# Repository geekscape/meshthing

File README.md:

meshthing
=========

MeshThing module: Hardware and software repository

Current version is v1.2.

Contents:
----------
-Hardware - Source files for PCB production.

-Software - Source files for testing and use.

-Resources - Additional utilities and documentation.

-Reference - Mostly datasheets.

Pinout:

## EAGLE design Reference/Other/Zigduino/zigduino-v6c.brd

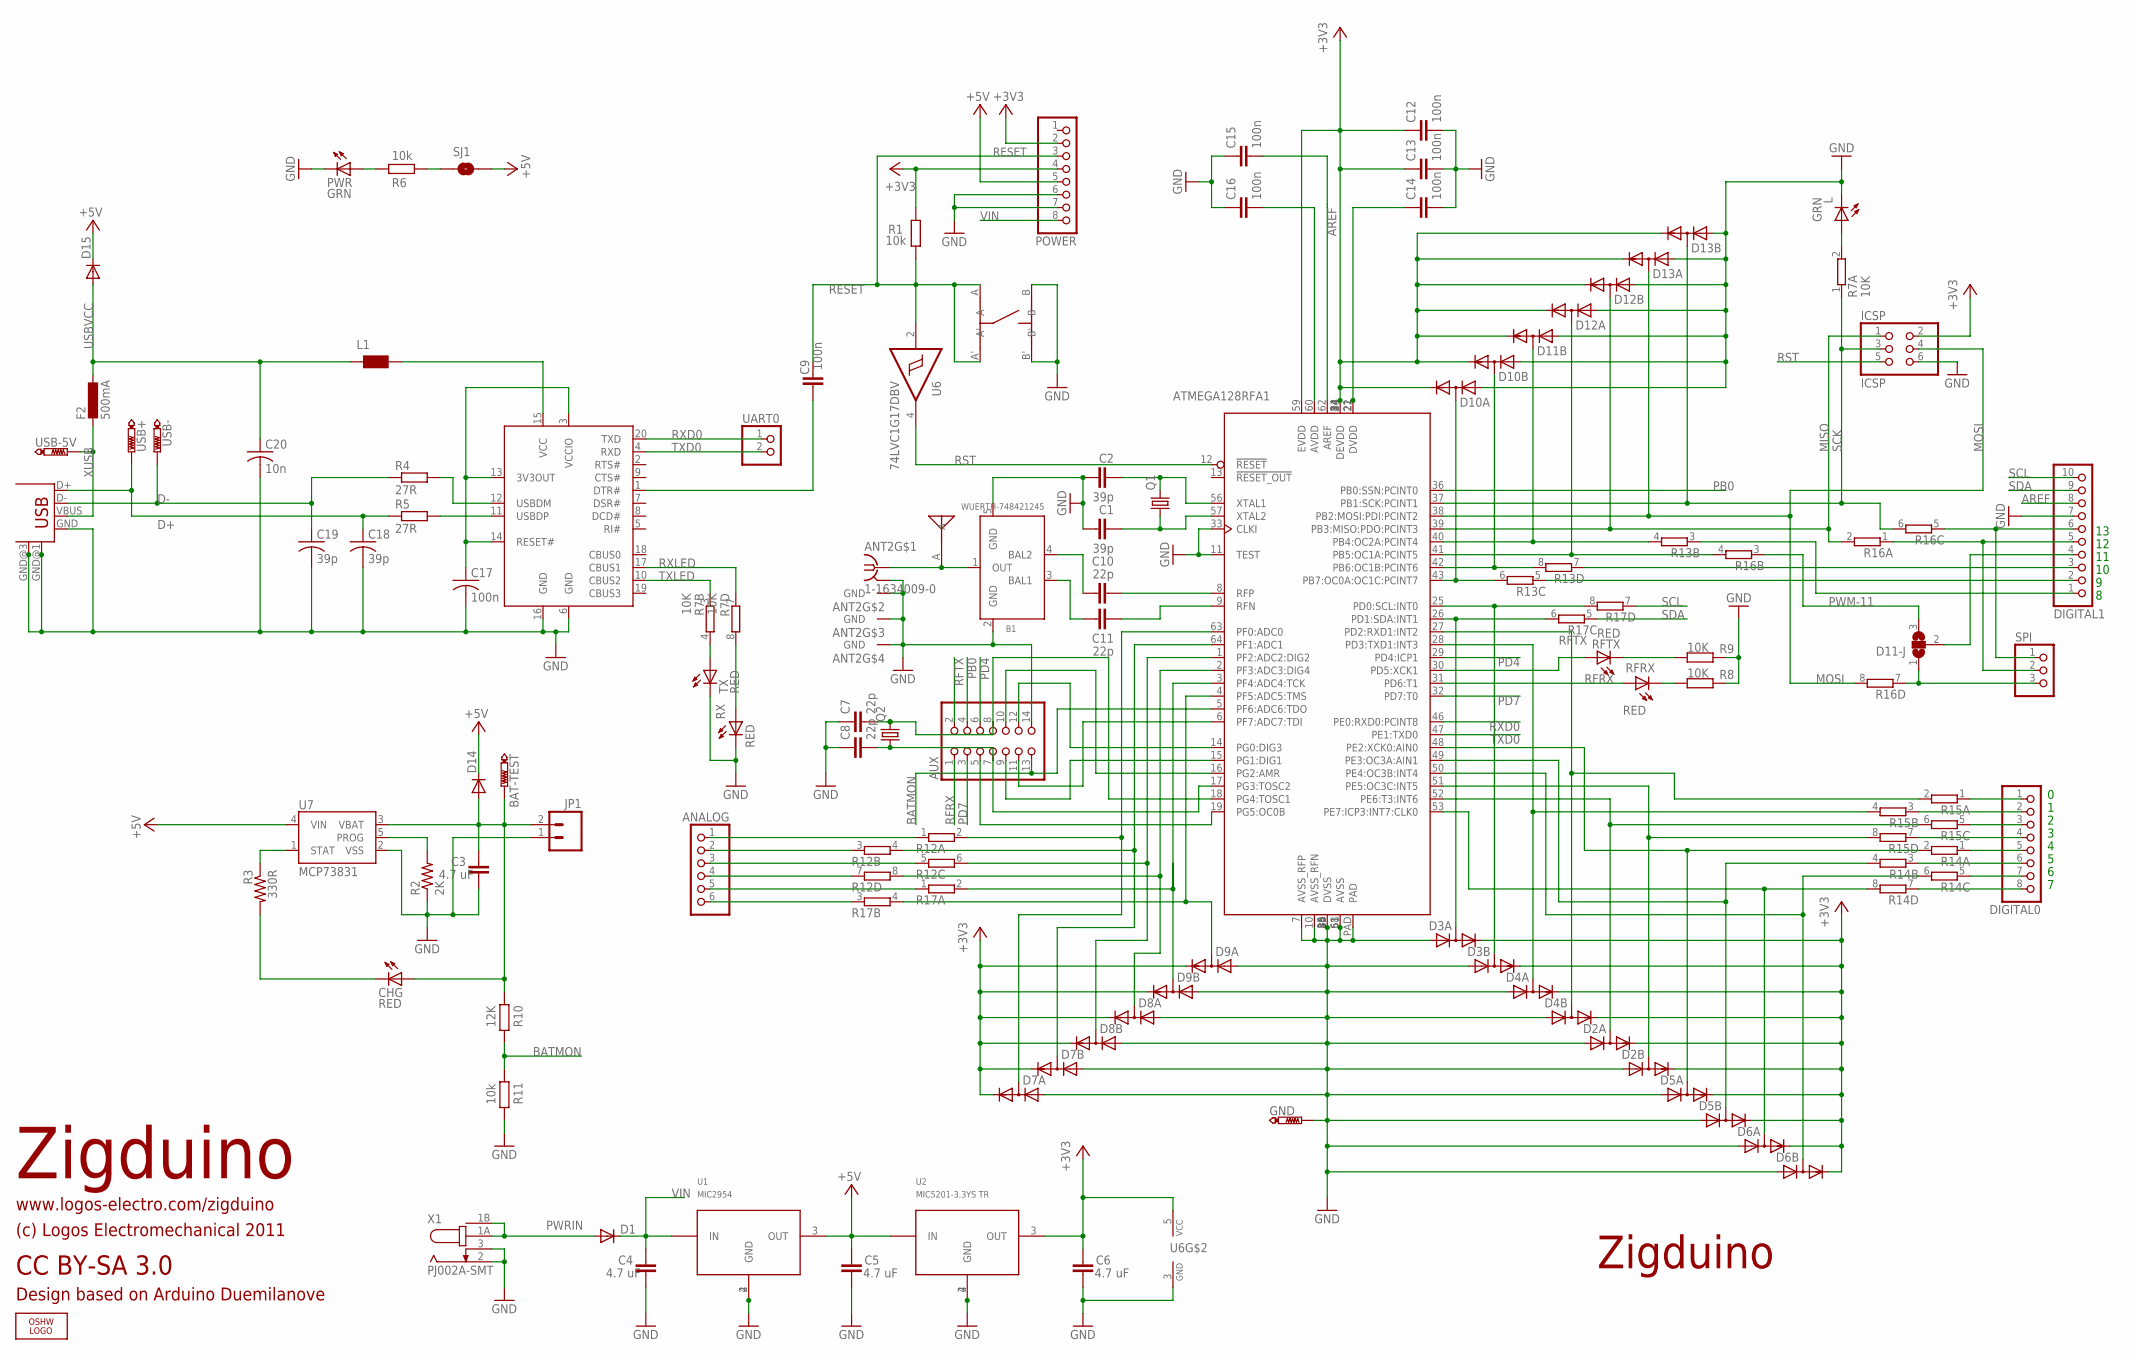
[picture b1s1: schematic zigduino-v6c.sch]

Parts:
ANALOG: PINHD-1X6; 1X06; PARTNO 19742
ANT1: MOLEX-ANT; PARTNO 0479480001
ANT2: 1-1634009-0; MMCX-THRU
AUX: PINHD-2X7_2.00; 2X07M; PARTNO 00217
B1: WUERTH-748421245; WURTH-BALUN; PARTNO 748421245
BAT-TEST: PTR1TP13SQ; TP13SQ; PARTNO TP13
C1, C2, C18, C19: 39p; C0603; PARTNO C1608C0G1H390J
C3, C4, C5, C6: 4.7 uF; C1206; PARTNO C3216Y5V1H475Z
C7, C8, C10, C11: 22p; C0603; PARTNO GQM1885C1H220JB01D
C9, C12, C13, C14, C15, C16, C17: 100n; C0603; PARTNO CC0603MRY5V9BB104
C20: 10n; C0603; PARTNO GRM188R71H103KA01D
CHG: RED; CHIP-LED0603; PARTNO LTST-C193KRKT-5A
D1, D14, D15: DIODE-SMB; SMB; PARTNO B150B-13-F
D2, D3, D4, D5, D6, D7, D8, D9, D10, D11, D12, D13: SD103ASDM; SOT26; PARTNO SD103ASDM-7
D11-J: SJ2W; SJ_2; PARTNO SJ3
DIGITAL0: PINHD-1X8; 1X08; PARTNO 19743
DIGITAL1: PINHD-1X10; 1X10; PARTNO 20083
F2: 500mA; L1812; PARTNO MF-MSMF050-2
GND: PTR1TP13SQ; TP13SQ; PARTNO TP13
ICSP: ICSP; 2X03; PARTNO 961206-6404-AR
JP1: M02-JST-2MM-SMT; S2B-PH; PARTNO S2B-PH-SM4-TB(LF)(SN)
L: GRN; CHIP-LED0603; PARTNO LTST-C193KGKT-5A
L1: WE-CBF_0805; 0805; PARTNO MI0805K400R-10
LOGO1: OSHW_LOGO_FILLX0200-NT; OSHW_FILLX200_NOTEXT
POWER: PINHD-1X8; 1X08; PARTNO 19743
PWR: GRN; CHIP-LED0603; PARTNO LTST-C193KGKT-5A
Q1: CRYSTALCSM-3X; CSM-3X; PARTNO ECS-160-20-3X-TR
Q2: CRYSTALTC26H; TC26H
R1, R6, R11: 10k; R0603; PARTNO RMCF0603FT10K0
R2: 2K; R0603; PARTNO RC0603FR-072KL
R3: 330R; R0603; PARTNO RC0603FR-07330RL
R4, R5: 27R; R0603; PARTNO RC0603JR-0727RL
R7: 10K; CTS742C083-RES; PARTNO 742C083103JPTR
R8, R9: 10K; R0603; PARTNO RMCF0603FT10K0
R10: 12K; R0603; PARTNO RMCF0603FT12K0
R12, R13, R14, R15, R16, R17: 4R-NCTS742C083; CTS742C083-RES; PARTNO 742C083101JPTR
RFRX: RED; CHIP-LED0603; PARTNO LTST-C193KRKT-5A
RFTX: RED; CHIP-LED0603; PARTNO LTST-C193KRKT-5A
RX: RED; CHIP-LED0603; PARTNO LTST-C193KRKT-5A
SJ1: SOLDERJUMPERTRACE; SJ_2S-TRACE
SPI: PINHD-1X3; 1X03; PARTNO 20152
SW1: EVQ-PSD02K; EVQPSD02K; PARTNO EVQ-PSD02K
TX: RED; CHIP-LED0603; PARTNO LTST-C193KRKT-5A
U1: MIC2954; SOT223; PARTNO MIC2954-03WS-TR
U2: MIC5201-3.3YS TR; SOT223; PARTNO MIC5201-3.3YS TR
U3: ATMEGA128RFA1; QFN64; PARTNO ATMEGA128RFA1-ZUR
U4: FT231XS-R; SSOP20; PARTNO FT231XS-R
U6: 74LVC1G17DBV; SOT23-5; PARTNO SN74LVC1G17DBVR
U7: MCP73831; SOT23-5; PARTNO MCP73831T-2ACI/OT
UART0: PINHD-1X2; 1X02; PARTNO 00522
USB: USB-MB-S; PARTNO 20236
USB+: PTR1TP13SQ; TP13SQ; PARTNO TP13
USB-, USB-5V: PTR1TP13SQ; TP13SQ; PARTNO TP13
X1: PJ002A-SMT; PARTNO PJ-002AH-SMT

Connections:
+3V3: C6.1, C12.1, C13.1, D2.2 (C), D2.5 (C), D3.2 (C), D3.5 (C), D4.2 (C), D4.5 (C), D5.2 (C), D5.5 (C), D6.2 (C), D6.5 (C), D7.2 (C), D7.5 (C), D8.2 (C), D8.5 (C), D9.2 (C), D9.5 (C), D10.2 (C), D10.5 (C), D11.5 (C), D12.2 (C), D12.5 (C), D13.2 (C), D13.5 (C), ICSP.2, POWER.2, POWER.4, R1.2, U2.3 (OUT), U3.23 (DEVDD), U3.34 (DEVDD), U3.44 (DEVDD), U3.54 (DEVDD), U3.59 (EVDD), U6.5 (VCC)
+5V: C5.1, D14.C, D15.C, POWER.5, SJ1.2, U1.3 (OUT), U2.1 (IN), U7.4 (VIN)
AREF: C15.2, DIGITAL1.8, U3.62 (AREF)
BATMON: AUX.13, R10.2, R11.1, U3.5 (PF6:ADC6:TDO)
D+: C18.1, R5.1, USB.D+, USB+.TP
D-: C19.1, R4.1, USB.D-, USB-.TP
DTR: C9.1, U4.1 (DTR#)
GND: ANT2.G@0 (GND), ANT2.G@1 (GND), ANT2.G@2 (GND), ANT2.G@3 (GND), AUX.14, B1.2 (GND), B1.5 (GND), C1.1, C2.1, C3.2, C4.2, C5.2, C6.2, C7.1, C8.1, C12.2, C13.2, C14.2, C15.1, C16.1, C17.2, C18.2, C19.2, C20.2, D2.3 (A), D2.6 (A), D3.3 (A), D3.6 (A), D4.3 (A), D4.6 (A), D5.3 (A), D5.6 (A), D6.3 (A), D6.6 (A), D7.3 (A), D7.6 (A), D8.3 (A), D8.6 (A), D9.3 (A), D9.6 (A), D10.3 (A), D10.6 (A), D11.6 (A), D12.3 (A), D12.6 (A), D13.3 (A), D13.6 (A), DIGITAL1.7, GND.TP, ICSP.6, JP1.1, L.C, POWER.6, POWER.7, PWR.C, R2.1, R8.1, R9.1, R11.2, RX.C, SW1.B, SW1.B', TX.C, U1.2 (GND), U1.4 (GND), U2.2 (GND), U2.4 (GND), U3.7 (AVSS_RFP), U3.10 (AVSS_RFN), U3.11 (TEST), U3.20 (DVSS), U3.24 (DVSS), U3.33 (CLKI), U3.35 (DVSS), U3.45 (DVSS), U3.55 (DVSS), U3.58 (AVSS), U3.61 (AVSS), U3.PAD, U4.6 (GND), U4.16 (GND), U6.3 (GND), U7.2 (VSS), USB.GND, USB.GND@1 (GND), USB.GND@3 (GND), X1.2, X1.3
MISO: D12.1 (AC), ICSP.1, R16.2, U3.39 (PB3:MISO:PDO:PCINT3)
MOSI: D13.4 (AC), ICSP.4, R16.8 (2), U3.38 (PB2:MOSI:PDI:PCINT2)
MOSI-PIN: D11-J.1, R16.7 (1), SPI.3
unnamed: R9.2, RFTX.C
unnamed: L.A, R7.2
unnamed: PWR.A, R6.2
unnamed: B1.4 (BAL2), C10.1
unnamed: DIGITAL0.3, R15.5 (1)
unnamed: C1.2, Q1.1, U3.57 (XTAL2)
unnamed: C2.2, Q1.2, U3.56 (XTAL1)
unnamed: R6.1, SJ1.1
unnamed: B1.3 (BAL1), C11.1
unnamed: DIGITAL1.5, R16.1, SPI.2
unnamed: DIGITAL0.5, R14.1
unnamed: DIGITAL0.7, R14.5 (1)
unnamed: DIGITAL0.6, R14.3 (1)
unnamed: DIGITAL0.4, R15.7 (1)
unnamed: DIGITAL0.8, R14.7 (1)
unnamed: D3.1 (AC), R17.8 (2), U3.25 (PD0:SCL:INT0)
unnamed: D3.4 (AC), R17.6 (2), U3.26 (PD1:SDA:INT1)
unnamed: ANT1.A, ANT2.C (1), B1.1 (OUT)
unnamed: D12.4 (AC), R16.4 (2), U3.41 (PB5:OC1A:PCINT5)
unnamed: R8.2, RFRX.C
unnamed: D2.4 (AC), R15.6 (2), U3.52 (PE6:T3:INT6)
unnamed: D2.1 (AC), R15.8 (2), U3.51 (PE5:OC3C:INT5)
unnamed: C10.2, U3.8 (RFP)
unnamed: C11.2, U3.9 (RFN)
unnamed: DIGITAL1.6, R16.5 (1), SPI.1
unnamed: R2.2, U7.5 (PROG)
unnamed: R3.1, U7.1 (STAT)
unnamed: CHG.C, R3.2
unnamed: C17.1, U4.3 (VCCIO), U4.13 (3V3OUT), U4.14 (RESET#)
unnamed: R7.4 (2), TX.A
unnamed: R7.8 (2), RX.A
unnamed: D11.1 (AC), R13.4 (2), U3.40 (PB4:OC2A:PCINT4)
unnamed: R4.2, U4.12 (USBDM)
unnamed: R5.2, U4.11 (USBDP)
unnamed: L1.2, U4.15 (VCC)
unnamed: D10.1 (AC), R13.8 (2), U3.42 (PB6:OC1B:PCINT6)
unnamed: D10.4 (AC), R13.6 (2), U3.43 (PB7:OC0A:OC1C:PCINT7)
unnamed: D5.4 (AC), R14.2, U3.48 (PE2:XCK0:AIN0)
unnamed: D6.1 (AC), R14.6 (2), U3.50 (PE4:OC3B:INT4)
unnamed: D5.1 (AC), R14.4 (2), U3.49 (PE3:OC3A:AIN1)
unnamed: D6.4 (AC), R14.8 (2), U3.53 (PE7:ICP3:INT7:CLK0)
unnamed: ANALOG.5, R17.1
unnamed: ANALOG.6, R17.3 (1)
unnamed: AUX.11, U3.6 (PF7:ADC7:TDI)
unnamed: D7.4 (AC), R12.2, U3.63 (PF0:ADC0)
unnamed: D7.1 (AC), R12.4 (2), U3.64 (PF1:ADC1)
unnamed: D8.1 (AC), R12.6 (2), U3.1 (PF2:ADC2:DIG2)
unnamed: D8.4 (AC), R12.8 (2), U3.2 (PF3:ADC3:DIG4)
unnamed: D9.1 (AC), R17.2, U3.3 (PF4:ADC4:TCK)
unnamed: D9.4 (AC), R17.4 (2), U3.4 (PF5:ADC5:TMS)
unnamed: ANALOG.1, R12.1
unnamed: ANALOG.2, R12.3 (1)
unnamed: ANALOG.3, R12.5 (1)
unnamed: ANALOG.4, R12.7 (1)
unnamed: DIGITAL1.1, R13.3 (1)
unnamed: D11-J.2, DIGITAL1.4
unnamed: AUX.12, U3.14 (PG0:DIG3)
unnamed: C14.1, U3.21 (DVDD), U3.22 (DVDD)
unnamed: C16.2, U3.60 (AVDD)
unnamed: DIGITAL1.2, R13.5 (1)
unnamed: DIGITAL0.1, R15.1
unnamed: DIGITAL0.2, R15.3 (1)
unnamed: AUX.9, U3.15 (PG1:DIG1)
unnamed: AUX.5, U3.19 (PG5:OC0B)
unnamed: AUX.8, C7.2, Q2.2, U3.18 (PG4:TOSC1)
unnamed: AUX.7, C8.2, Q2.1, U3.17 (PG3:TOSC2)
unnamed: AUX.10, U3.16 (PG2:AMR)
PB0: AUX.4, U3.36 (PB0:SSN:PCINT0)
PD4: AUX.6, U3.29 (PD4:ICP1)
PD7: AUX.3, U3.32 (PD7:T0)
PWM-10: DIGITAL1.3, R13.7 (1)
PWM-11: D11-J.3, R16.3 (1)
PWRIN: D1.A, X1.1A, X1.1B
RESET: C9.2, POWER.3, R1.1, SW1.A, SW1.A', U6.2 (I)
RFRX: AUX.1, RFRX.A, U3.31 (PD6:T1)
RFTX: AUX.2, RFTX.A, U3.30 (PD5:XCK1)
RST: ICSP.5, U3.12 (!RESET!), U6.4 (O)
RXD0: U3.46 (PE0:RXD0:PCINT8), U4.20 (TXD), UART0.1
RXD1: D4.1 (AC), R15.2, U3.27 (PD2:RXD1:INT2)
RXLED: R7.7 (1), U4.17 (CBUS1)
SCK: D13.1 (AC), ICSP.3, R7.1, R16.6 (2), U3.37 (PB1:SCK:PCINT1)
SCL: DIGITAL1.10, R17.7 (1)
SDA: DIGITAL1.9, R17.5 (1)
TXD0: U3.47 (PE1:TXD0), U4.4 (RXD), UART0.2
TXD1: D4.4 (AC), R15.4 (2), U3.28 (PD3:TXD1:INT3)
TXLED: R7.3 (1), U4.10 (CBUS2)
USBVCC: C20.1, D15.A, F2.1, L1.1
VBAT: BAT-TEST.TP, C3.1, CHG.A, D14.A, JP1.2, R10.1, U7.3 (VBAT)
VIN: C4.1, D1.C, POWER.8, U1.1 (IN)
XUSB: F2.2, USB.VBUS, USB-5V.TP

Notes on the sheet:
Zigduino
CC BY-SA 3.0
(c) Logos Electromechanical 2011
www.logos-electro.com/zigduino
ATMEGA128RFA1
Design based on Arduino Duemilanove

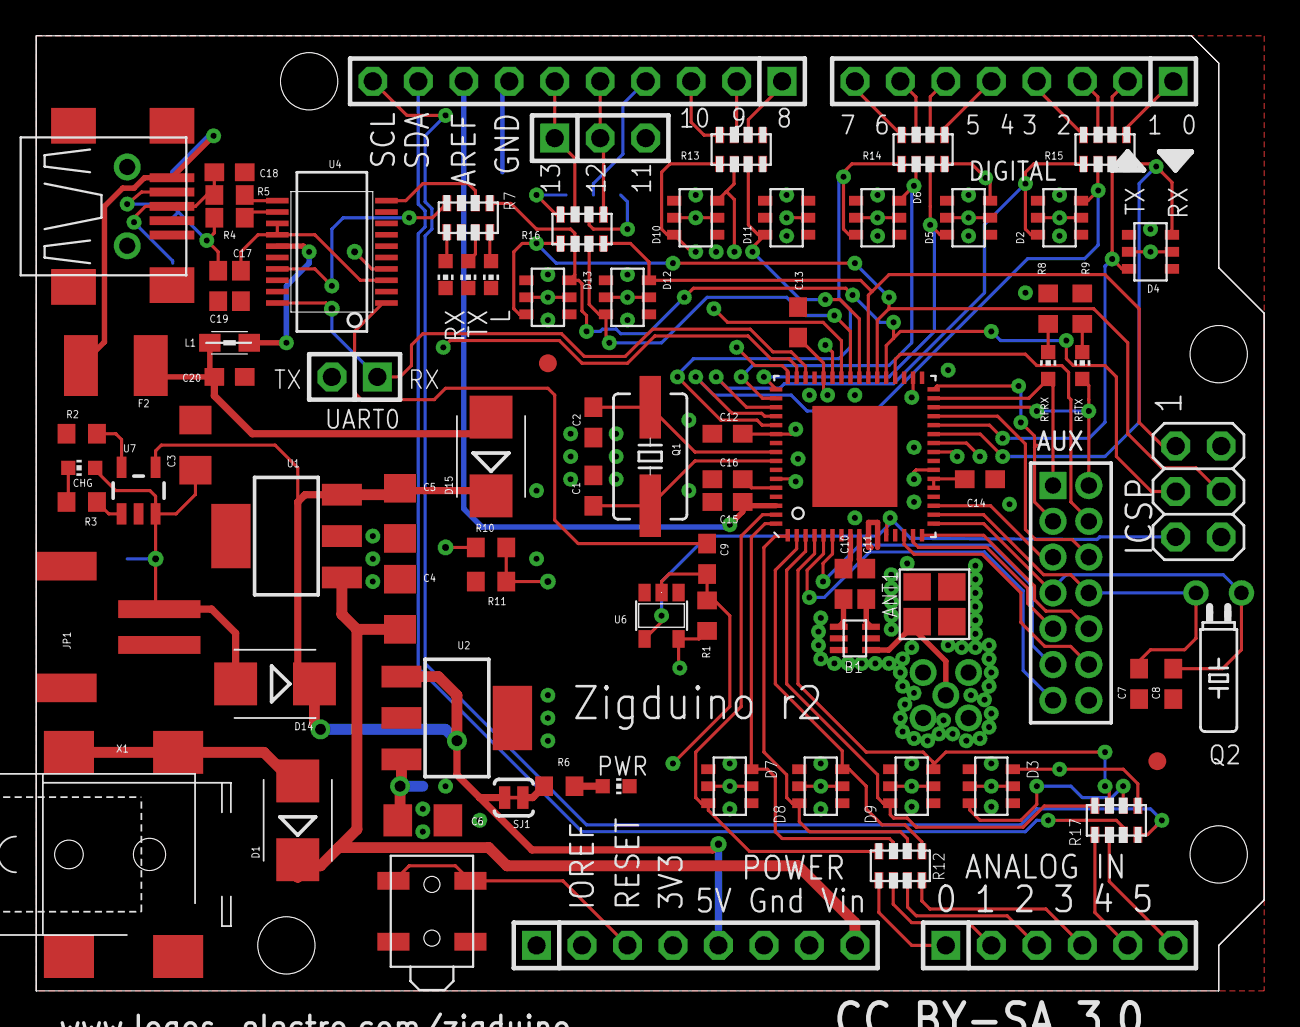
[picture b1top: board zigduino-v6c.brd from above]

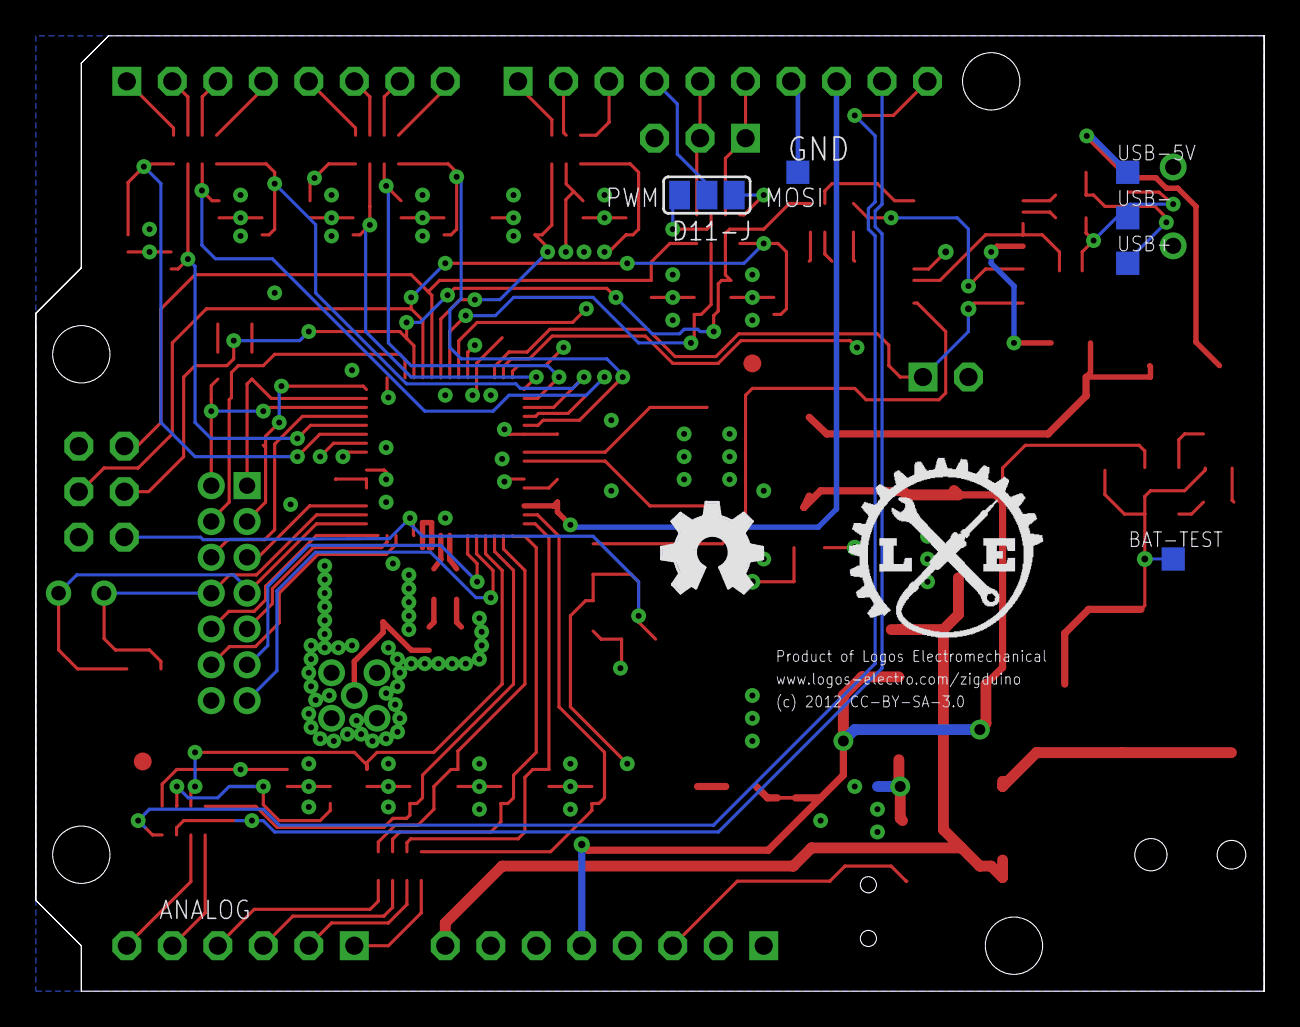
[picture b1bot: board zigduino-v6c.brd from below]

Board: 4 copper layers, 68.6 x 53.3 mm, 95 parts (8 on the bottom side), 101 nets.

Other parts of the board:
U$3, U$5: FIDUCIAL_G10
U$4: LOGO-SM

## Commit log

2013-09-16 Commit v1.1.
2013-10-15 Begin v1.2. Cleanup done.
2013-10-17 V1.2 nearly done. Alignment marks needed.
2013-10-18 More checks.
2013-10-18 Removing Archive folder from git tracking.
2013-10-18 Removing Ref folder from tracking.
2013-10-18 Untracking folders.
2013-10-18 error.
2013-10-18 Readme.
2013-10-18 Fiducials added, refining positions.
2013-10-22 v1.2 Production.
2013-11-07 Bootloader for >=v1.1.
2013-11-14 Adding back reference documents to repo.
2013-11-14 Remove "*~" files.
2013-11-15 Moving things around and documenting them.
2013-11-15 Update README.
2013-11-15 Updating pins_arduino.h.
2013-11-15 First stab at a pinout poster.
2013-11-15 Somechanges to update Arduion pins.
2013-11-18 First crack at pinout poster.
2013-11-18 Pinout poster changes.
2013-11-18 Pinout .jpg.
2013-11-22 Software changes. Added pin exercise.
2013-11-22 Cleaning up.
2013-12-03 Updating some documentation.
2013-12-03 Reduce size of MTPinout.png
2013-12-05 TAPR Hardware License added.
2013-12-11 Typo on Pinout.
2013-12-11 Initial Firmata support and pins_arduino fixes.
2013-12-22 Final v1.2 commit.
2013-12-22 Initial v2.0 commit.
2013-12-22 README quick update.
2013-12-23 Minor.
2013-12-23 More minor fixes.
2013-12-23 Very nearly there.
2013-12-24 MeshWasp added.
2014-01-08 Logo work and branch to flip.
2014-01-08 Initial flip done.
2014-01-09 Mostly silks and initial documentation.
2014-01-09 Thicken pwr traces, mechanical relief on TH.
2014-01-09 Logo work.
2014-01-15 ICSP keepout recognized on MW. Silks, gerbers.
2014-01-18 Moved ATMega256RFR2 STK500 bootloader to new GitHub repository ... https://github.com/geekscape/stk500boot_atmega256rfr2
2014-01-22 Added some documentation/pinout graphics.
2014-01-24 Minor changes, initial positions file for MT.
2014-02-18 Removed ICSP pads.
2014-02-18 Annyoing files.
2014-02-18 Boards.txt
2014-03-05 Minor silks & logo work.
2014-03-05 Positions file and footprint pad drills to .7mm.
2014-03-05 MeshWasp positions & render.
2014-08-16 Updated some MW documentation.
2014-08-16 MW README.

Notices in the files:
Reference/Other/Zigduino/zigduino-v6c.brd:
(c) 2012 CC-BY-SA-3.0
parts and their libraries:
SparkFun: Licensing: CC v3.0 Share-Alike You are welcome to use this library for commercial purposes.
dicons: Copyright (C) 2004, Bob Starr (rtzaudio@mindspring.com)
